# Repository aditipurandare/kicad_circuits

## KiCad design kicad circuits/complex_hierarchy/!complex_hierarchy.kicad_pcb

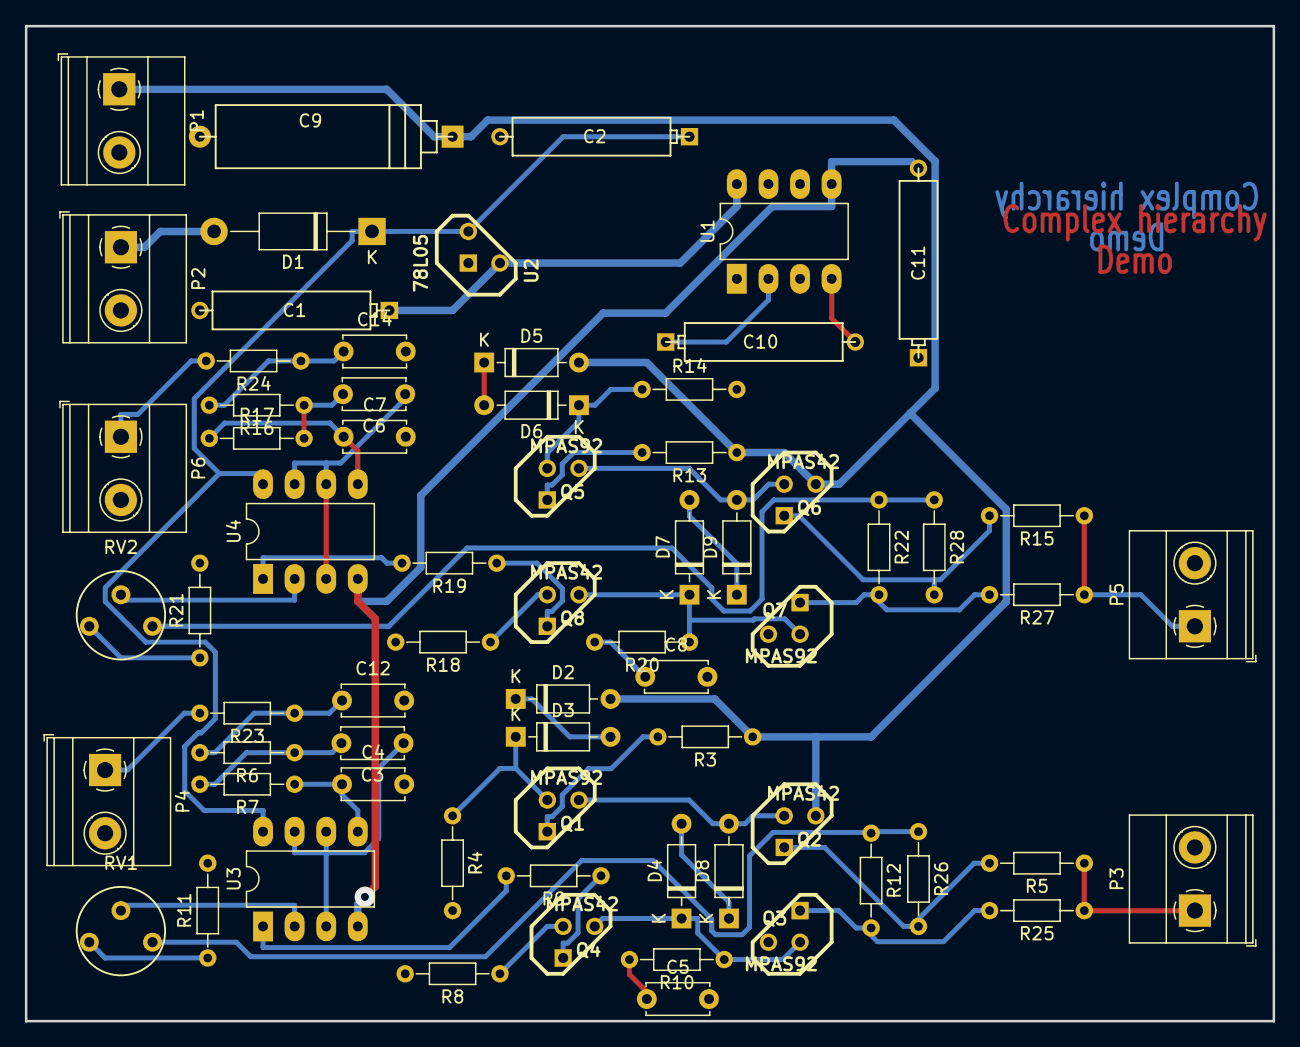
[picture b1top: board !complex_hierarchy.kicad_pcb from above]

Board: 2 copper layers, 100.3 x 80.0 mm, 68 parts (0 on the bottom side), 50 nets.

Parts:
C1: 47uF; CP6
C2: 47uF/20V; CP6
C3, C6: 15nF; C_Disc_D5.0mm_W2.5mm_P5.00mm
C4, C7: 4.7nF; C_Disc_D5.0mm_W2.5mm_P5.00mm
C5, C8: 820pF; C_Disc_D5.0mm_W2.5mm_P5.00mm
C9: 47uF/63V; CP8
C10, C11: 10uF; CP6
C12, C14: 150nF; C_Disc_D5.0mm_W2.5mm_P5.00mm
D1: 1N4007; D_DO-41_SOD81_P12.70mm_Horizontal
D2, D3, D4, D5, D6, D7, D8, D9: 1N4148; D_DO-35_SOD27_P7.62mm_Horizontal
P1, P2, P3, P4, P5, P6: CONN_2; TerminalBlock_Phoenix_MKDS-1,5-2-5.08_1x02_P5.08mm_Horizont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
Q1, Q3, Q5, Q7: MPAS92; TO92-CBE
Q2, Q4, Q6, Q8: MPAS42; TO92-CBE
R3, R13: 470; R_Axial_DIN0204_L3.6mm_D1.6mm_P7.62mm_Horizontal
R4, R12, R14, R22, R26, R28: 220K; R_Axial_DIN0204_L3.6mm_D1.6mm_P7.62mm_Horizontal
R5, R15, R25, R27: 47; R_Axial_DIN0204_L3.6mm_D1.6mm_P7.62mm_Horizontal
R6, R7, R16, R17: 22K; R_Axial_DIN0204_L3.6mm_D1.6mm_P7.62mm_Horizontal
R8, R9, R18, R19, R23, R24: 1K; R_Axial_DIN0204_L3.6mm_D1.6mm_P7.62mm_Horizontal
R10, R20: 5,6K; R_Axial_DIN0204_L3.6mm_D1.6mm_P7.62mm_Horizontal
R11, R21: 4,7K; R_Axial_DIN0204_L3.6mm_D1.6mm_P7.62mm_Horizontal
RV1, RV2: 4,7K; RV2
U1: ICL7660; DIP-8_W7.62mm_LongPads
U2: 78L05; LM78LXX
U3, U4: LM358N; DIP-8_W7.62mm_LongPads

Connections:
+12C: C2.1, D1.1, U2.VI, U3.8, U4.8
-VAA: C11.2, U1.5, U3.4, U4.4
/12Vext: D1.2, P2.1
/ampli_ht_horizontal/PIEZO_IN: P6.1, R24.2
/ampli_ht_horizontal/PIEZO_OUT: P5.1, R15.1, R27.1
/ampli_ht_horizontal/S_OUT+: R22.1, R28.1, RV2.3
/ampli_ht_horizontal/Vpil_0_3,3V: C6.1, U4.3, U4.6, U4.7
/ampli_ht_vertical/PIEZO_IN: P4.1, R23.2
/ampli_ht_vertical/PIEZO_OUT: P3.1, R5.1, R25.1
/ampli_ht_vertical/S_OUT+: R12.1, R26.1, RV1.3
/ampli_ht_vertical/Vpil_0_3,3V: C3.1, U3.3, U3.6, U3.7
GND: C1.2, C2.2, C4.2, C5.2, C7.2, C8.2, C9.2, C11.1, C12.2, C14.2, P1.2, P2.2, P3.2, P4.2, P5.2, P6.2, Q3.C, Q7.C, R4.2, R8.2, R11.2, R14.2, R18.2, R21.2, U1.3, U2.GND
HT: C9.1, D2.2, D5.2, P1.1, Q2.C, Q6.C, R3.1, R13.1
unnamed: C3.2, R6.1, R7.2
unnamed: C4.1, R7.1, U3.5
unnamed: C5.1, R10.2
unnamed: C6.2, R16.1, R17.2
unnamed: C7.1, R17.1, U4.5
unnamed: C8.1, R20.2
unnamed: C10.1, U1.2
unnamed: C10.2, U1.4
unnamed: C12.1, R6.2, R23.1
unnamed: C14.1, R16.2, R24.1
unnamed: D2.1, D3.2
unnamed: D3.1, Q1.B, R4.1
unnamed: D4.1, Q3.B, Q4.C, R10.1
unnamed: D4.2, D8.1
unnamed: D5.1, D6.2
unnamed: D6.1, Q5.B, R14.1
unnamed: D7.1, Q7.B, Q8.C, R20.1
unnamed: D7.2, D9.1
unnamed: D8.2, Q1.C, Q2.B
unnamed: D9.2, Q5.C, Q6.B
unnamed: Q1.E, R3.2
unnamed: Q2.E, R5.2, R26.2
unnamed: Q3.E, R12.2, R25.2
unnamed: Q4.B, R8.1
unnamed: Q4.E, R9.1
unnamed: Q5.E, R13.2
unnamed: Q6.E, R15.2, R28.2
unnamed: Q7.E, R22.2, R27.2
unnamed: Q8.B, R18.1
unnamed: Q8.E, R19.1
unnamed: R9.2, U3.1
unnamed: R11.1, RV1.1
unnamed: R19.2, U4.1
unnamed: R21.1, RV2.1
unnamed: RV1.2, U3.2
unnamed: RV2.2, U4.2
VCC: C1.1, U1.8, U2.VO

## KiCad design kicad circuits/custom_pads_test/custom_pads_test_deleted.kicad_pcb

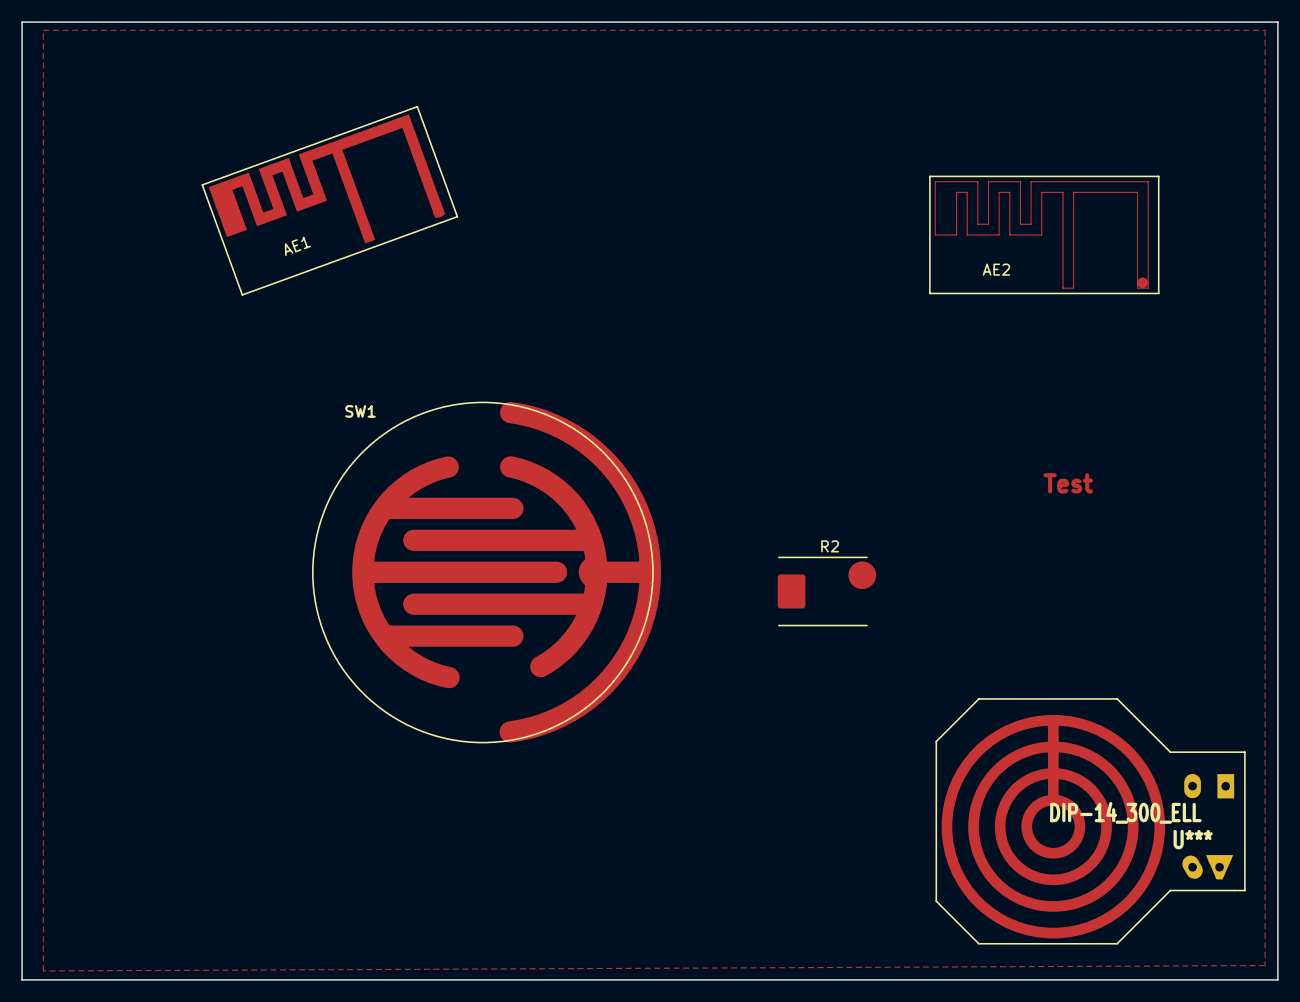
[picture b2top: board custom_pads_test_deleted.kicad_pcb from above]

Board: 2 copper layers, 118.0 x 90.0 mm, 5 parts (0 on the bottom side), 3 nets, no tracks yet.

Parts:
AE1, AE2: Antenna; 1pin
R2: R; DO-214AB
SW1: R; C2
U***: DIP-14_300_ELL; DIP-14__300_ELL

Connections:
/PAD1: R2.1, SW1.1
/PAD2: R2.2, SW1.2
GND: AE1.1, AE2.1

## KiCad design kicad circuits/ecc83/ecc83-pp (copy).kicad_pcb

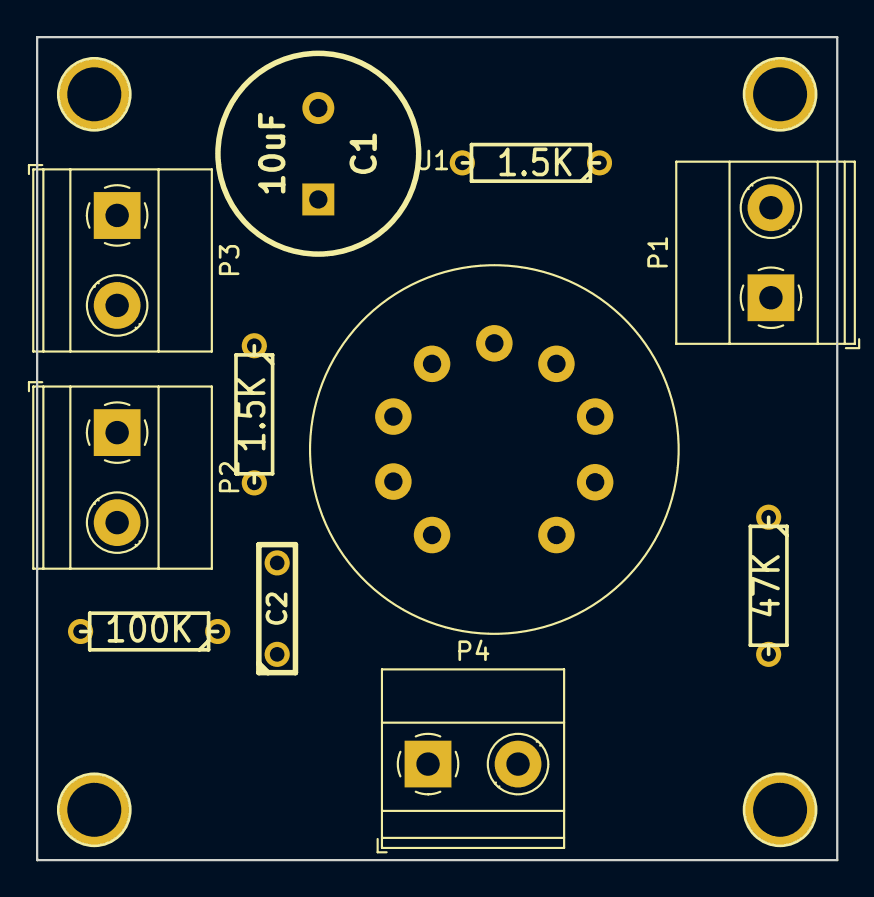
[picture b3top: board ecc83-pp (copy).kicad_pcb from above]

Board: 2 copper layers, 44.5 x 45.7 mm, 15 parts (0 on the bottom side), 9 nets, no tracks yet.

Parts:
C1: 10uF; C2V10
C2: 680nF; C2
P1: IN; TerminalBlock_Phoenix_MKDS-1,5-2_1x02_P5.00mm_Horizontal
P2: OUT; TerminalBlock_Phoenix_MKDS-1,5-2_1x02_P5.00mm_Horizontal
P3: POWER; TerminalBlock_Phoenix_MKDS-1,5-2_1x02_P5.00mm_Horizontal
P4: CONN_2; TerminalBlock_Phoenix_MKDS-1,5-2_1x02_P5.00mm_Horizontal
P5, P6, P7, P8: CONN_1; 1pin
R1, R2: 1.5K; R3
R3: 100K; R3
R4: 47K; R3
U1: ECC83; Valve_ECC-83-1

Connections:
GND: C1.2, P1.1, P2.2, P3.2, R2.2, R3.2, R4.2
unnamed: C1.1, P3.1, U1.6
unnamed: C2.1, P2.1, R3.1
unnamed: C2.2, R1.2, U1.8
unnamed: P1.2, R4.1, U1.2
unnamed: P4.1, U1.9
unnamed: P4.2, U1.4, U1.5
unnamed: R1.1, U1.1, U1.7
unnamed: R2.1, U1.3

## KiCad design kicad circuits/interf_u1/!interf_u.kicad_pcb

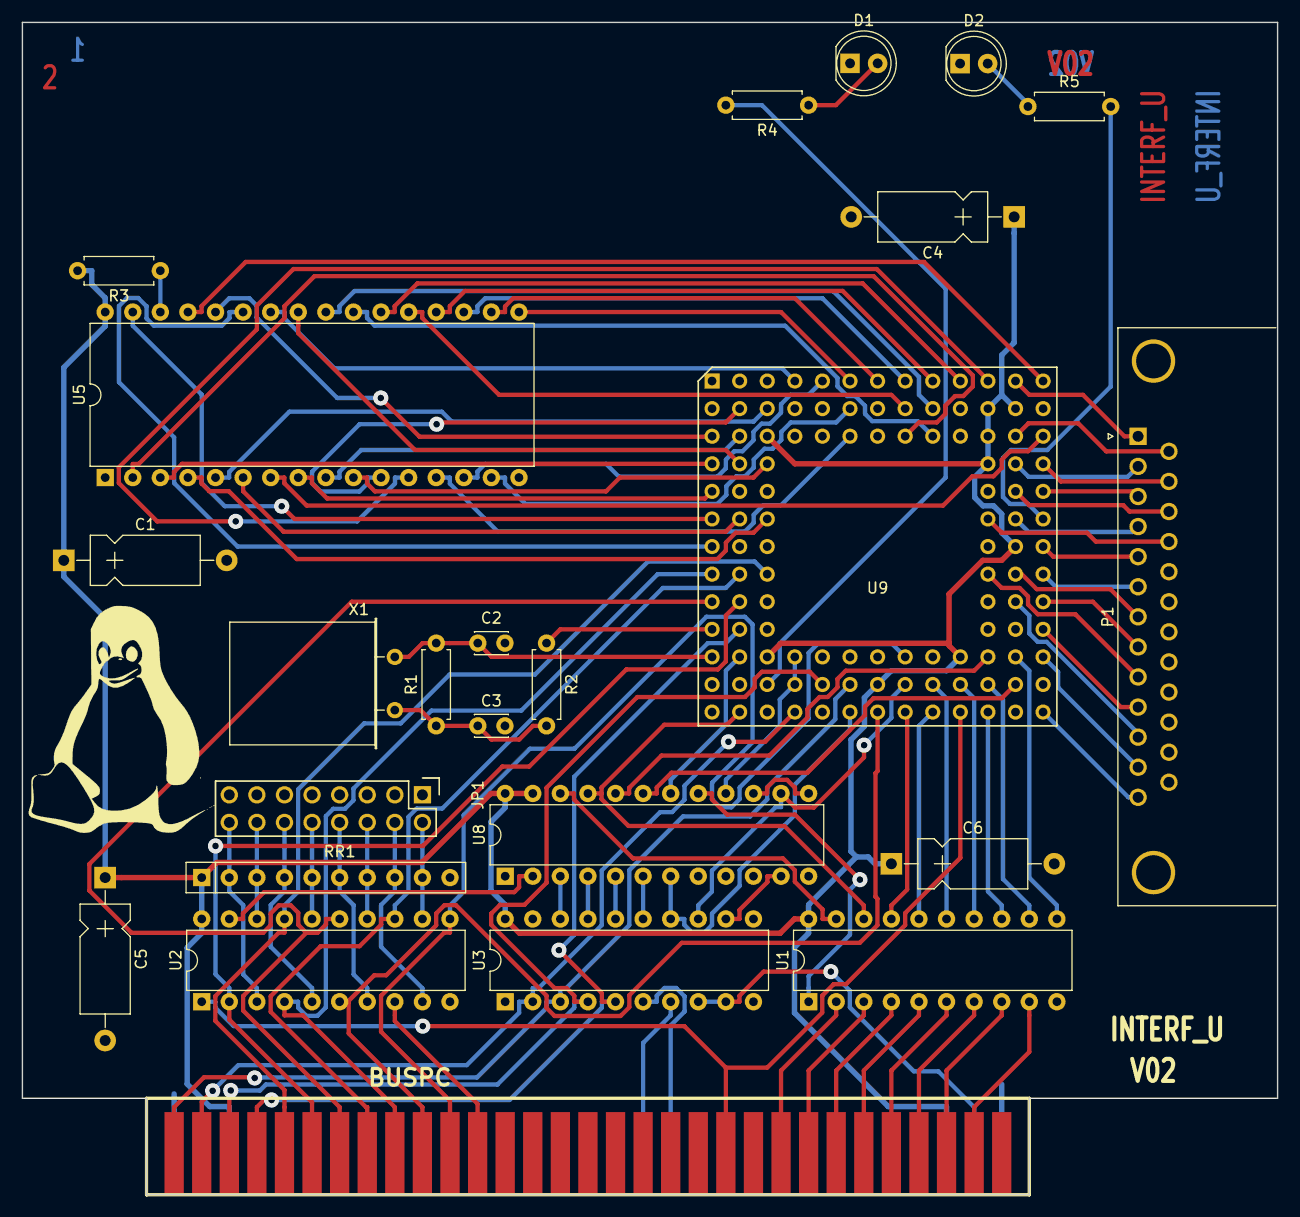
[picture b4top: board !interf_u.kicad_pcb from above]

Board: 2 copper layers, 115.6 x 108.0 mm, 25 parts (0 on the bottom side), 110 nets.

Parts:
BUS1: BUSPC; BUS_PC
C1, C4, C5, C6: 47uF; CP_Axial_L10.0mm_D4.5mm_P15.00mm_Horizontal
C2, C3: 47pF; C_Disc_D3.0mm_W2.0mm_P2.50mm
D1, D2: LED; LED_D5.0mm
G1: Tux; LOGO
JP1: CONN_8X2; Pin_Header_Straight_2x08
P1: DB25FEMELLE; DSUB-25_Female_Horizontal_P2.77x2.84mm_EdgePinOffset9.90mm_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
R1: 100K; R_Axial_DIN0207_L6.3mm_D2.5mm_P7.62mm_Horizontal
R2: 1K; R_Axial_DIN0207_L6.3mm_D2.5mm_P7.62mm_Horizontal
R3: 10K; R_Axial_DIN0207_L6.3mm_D2.5mm_P7.62mm_Horizontal
R4, R5: 330; R_Axial_DIN0207_L6.3mm_D2.5mm_P7.62mm_Horizontal
RR1: 9x1K; R_Array_SIP10
U1: 74LS245; DIP-20_W7.62mm
U2: 74LS688; DIP-20_W7.62mm
U3: 74LS541; DIP-20_W7.62mm
U5: 628128; DIP-32_W15.24mm
U8: EP600; DIP-24_W7.62mm
U9: 4003APG120; PGA120
X1: 8MHz; Crystal_HC18-U_Horizontal

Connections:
/8MH-OUT: R2.1, U9.K1
/ACK: P1.10, U9.K13
/AUTOFD-: P1.14, U9.C12
/BIT0: P1.2, U9.D12
/BIT1: P1.3, U9.E13
/BIT2: P1.4, U9.F12
/BIT3: P1.5, U9.G13
/BIT4: P1.6, U9.H13
/BIT5: P1.7, U9.H12
/BIT6: P1.8, U9.J13
/BIT7: P1.9, U9.H11
/BUST+: P1.11, U9.J12
/CLKLCA: U8.16, U9.L4, U9.M4
/CS1-: U5.22, U9.A10
/D0: U1.18, U8.21, U9.N2
/D1: U1.17, U9.N8
/D2: U1.16, U9.N9
/D3: U1.15, U9.M9
/D4: U1.14, U9.M10
/D5: U1.13, U9.N11
/D6: U1.12, U9.M11
/D7: U1.11, U9.L12
/DIR: U1.1, U8.17
/DONE: U8.20, U9.L11
/ENBBUF: U1.19, U8.22
/ERROR-: P1.15, U9.D13
/INIT-: P1.16, U9.E12
/LED1: R4.2, U9.M3
/LED2: R5.2, U9.F13
/MA0: U5.12, U9.A11
/MA1: U5.11, U9.B2
/MA2: U5.10, U9.D3
/MA3: U5.9, U9.C2
/MA4: U5.8, U9.E1
/MA5: U5.7, U9.C13
/MA6: U5.6, U9.F2
/MA7: U5.5, U9.B3
/MA8: U5.27, U9.G1
/MA9: U5.26, U9.A4
/MA10: U5.23, U9.C9
/MA11: U5.25, U9.D2
/MA12: U5.4, U9.F3
/MA13: U5.28, U9.C1
/MA14: U5.3, U9.D1
/MA15: U5.31, U9.F1
/MA16: U5.2, U9.C8
/MATCHL: U2.19, U8.2
/MD0: U5.13, U9.C6
/MD1: U5.14, U9.A5
/MD2: U5.15, U9.B6
/MD3: U5.17, U9.A6
/MD4: U5.18, U9.A7
/MD5: U5.19, U9.A8
/MD6: U5.20, U9.A9
/MD7: U5.21, U9.B8
/OE-: U5.24, U9.B9
/PC-A0: BUS1.62, U3.3, U9.M6
/PC-A1: BUS1.61, U3.2, U9.N4
/PC-A2: BUS1.60, U3.4, U9.M5
/PC-A3: BUS1.59, U3.5, U9.K2
/PC-A4: BUS1.58, U2.17, U9.H3
/PC-A5: BUS1.57, U2.2, U9.J2
/PC-A6: BUS1.56, U2.15, U9.J1
/PC-A7: BUS1.55, U2.13, U9.H2
/PC-A8: BUS1.54, U2.4, U9.H1
/PC-A9: BUS1.53, U2.6, U9.N7
/PC-A10: BUS1.52, U2.11, U9.L8
/PC-A11: BUS1.51, U2.8
/PC-AEN: BUS1.42, U2.1, U9.N10
/PC-DB0: BUS1.40, U1.2
/PC-DB1: BUS1.39, U1.3
/PC-DB2: BUS1.38, U1.4
/PC-DB3: BUS1.37, U1.5
/PC-DB4: BUS1.36, U1.6
/PC-DB5: BUS1.35, U1.7
/PC-DB6: BUS1.34, U1.8
/PC-DB7: BUS1.33, U1.9
/PC-IOR: BUS1.14, U3.7
/PC-IOW: BUS1.13, U3.6
/PC-RD: U3.13, U8.14, U9.M8
/PC-RST: BUS1.2, U3.8, U3.9
/PC-WR: U3.14, U8.7, U9.N6
/PE+: P1.12, U9.L13
/PROG-: U8.19, U9.M12
/REF4: JP1.14, RR1.3, U2.18
/REF5: JP1.16, RR1.2, U2.3
/REF6: JP1.10, RR1.5, U2.16
/REF7: JP1.6, RR1.7, U2.14
/REF8: JP1.12, RR1.4, U2.5
/REF9: JP1.8, RR1.6, U2.7
/REF10: JP1.2, RR1.9, U2.12
/REF11: JP1.4, RR1.8, U2.9
/RSTL: U3.12, U8.11
/SEL_LPT: U8.18, U9.L2
/SLCT+: P1.13, U9.N13
/SLCTIN-: P1.17, U9.F11
/STROBE: P1.1, U9.A12
/WR-: U5.29, U9.A13
/WR_REG: U8.13, U8.15
GND: BUS1.1, BUS1.31, C1.2, C2.2, C3.2, C4.2, C5.2, C6.2, D1.1, D2.1, JP1.1, JP1.3, JP1.5, JP1.7, JP1.9, JP1.11, JP1.13, JP1.15, P1.18, P1.19, P1.20, P1.21, P1.22, P1.23, P1.24, P1.25, U1.10, U2.10, U3.1, U3.10, U3.19, U5.16, U8.1, U8.12, U9.B7, U9.C4, U9.C10, U9.G2, U9.G11, U9.K3, U9.K11, U9.L7
unnamed: C2.1, R1.2, U9.L1, X1.1
unnamed: C3.1, R1.1, R2.2, X1.2
unnamed: D1.2, R4.1
unnamed: D2.2, R5.1
unnamed: R3.1, U5.30
unnamed: U3.15, U8.6
unnamed: U3.16, U8.5
unnamed: U3.17, U8.4
unnamed: U3.18, U8.3
VCC: BUS1.3, BUS1.29, C1.1, C4.1, C5.1, C6.1, R3.2, RR1.1, U1.20, U2.20, U3.20, U5.32, U8.23, U8.24, U9.B11, U9.B12, U9.C3, U9.C11, U9.D11, U9.G12, U9.L3, U9.L10, U9.M7

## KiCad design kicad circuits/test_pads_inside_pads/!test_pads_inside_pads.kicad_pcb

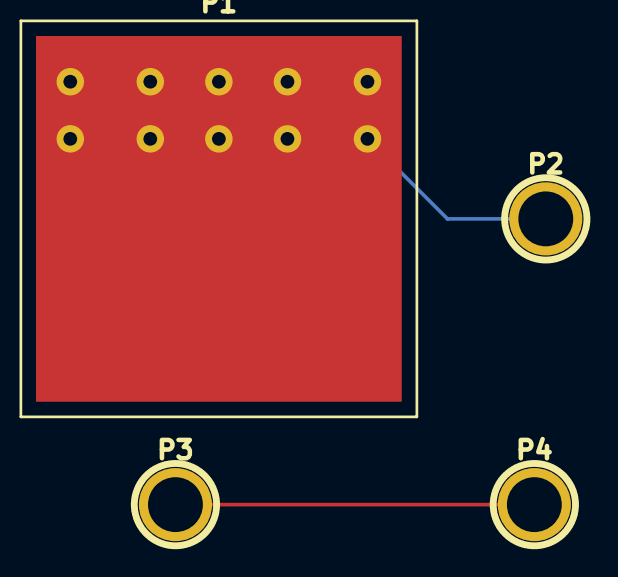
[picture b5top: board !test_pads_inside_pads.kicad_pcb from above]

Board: 2 copper layers, 4 parts (0 on the bottom side), 2 nets.

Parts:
P1, P2, P3, P4: CONN_1; 1pin

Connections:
/NET1: P3.1, P4.1
/NET2: P1.1, P2.1
